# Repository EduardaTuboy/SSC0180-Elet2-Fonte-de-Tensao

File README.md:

# Trabalho 1 - Fonte de tensão variável
Projeto realizado para a disciplina Eletrônica para Computação [SSC0180], ministrado pelo docente [Eduardo Vale Simões](https://gitlab.com/simoesusp), durante o primeiro semestre do curso de Bacharelado em Ciências de Computação, na USP campus São Carlos.

## Integrantes do Grupo 8
* [Eduarda tuboy Nardin](https://github.com/EduardaTNardin) | nº USP 13732495
* [Gabriel Barbosa dos Santos](https://github.com/GotemBarbosa) | nº USP 14613991
* [Guilherme Antonio Costa Bandeira](https://github.com/Guilherme-Bandeira) | nº USP 14575620
* [Rafael Brazolin Alvez Mansur](https://github.com/RafaelMansurUsp)| nº USP 14604020
* [Renan Parpinelli Scarpin](https://github.com/RenanScarpin)| nº USP 14712188

## Objetivo
Montar em uma *protoboard* um circuito que recebe como entrada uma corrente alternada de 127V e retorna como saída uma corrente contínua ajustável entre 3V a 12V, com capacidade de 100mA de corrente.

## Diagrama de fonte no Falstad

Link do circuito no Falstad [aqui](https://tinyurl.com/2mkt75e9).

## Escolha dos Componentes
Todos os componentes, menos o cabo conectado ao transformador, foram comprados na loja “Ca And Ma Componentes Eletrônicos”, localizada em São Carlos.

Quantidade | Componente | Especificações | Preço Unidade
--- | --- | --- | ---
1 | Transformador | Trafo Bivolt 18+18v 500mA | R$ 41,90
1 | Ponte Retificadora | KBP206 2A 600V Tower | R$ 3,80
1 | Capacitor | Elco 680 µF 25V | R$ 5,80
1 | LED | Cristal, cor vermelha | R$ 1,30
1 | Diodo Zenner | 1N47430 [ 13V \ 1W ] | R$ 0,48
1 | Transistor NPN | BD137 [ 60V \ 1,5A ] | R$ 1,40
1 | Potenciômetro 5K | 1W \ B5K | R$ 7,00
2 | Resistor 1K | CR25 Carvão LGE | R$ 0,14
1 | Resistor 2.7K | CR25 Carvão | R$ 0,07
1 | Resistor 6.8K | CR25 Carvão Rohs | R$ 0,07
10 | Jumpers | Femea x Macho | R$ 0,70
1 | Protoboard | BB-01 400P Sem base tower | R$ 20,40
Total | | | R$ 89,36

## Projeto no Software Eagle

## Cálculos e Montagem
De início, é necessário saber a razão Ns / Np, utilizado nas definições do Falstad, sendo Ns número de espiras do enrolamento da bobina secundária e Np número de espiras do enrolamento da bobina primária. Essa razão se dá pela relação:

$\frac{V_p}{N_p}=\frac{V_s}{N_s}$

$\frac{127}{N_p}=\frac{18}{N_s}$

$\frac{N_s}{N_p}=\frac{18}{127} = 7,05$

Depois, é calculada a tensão de pico do circuito, que é a voltagem que sai do transformador vezes raiz de dois subtraindo duas vezes o valor 0,7V, que é a quantidade de tensão dissipada por cada diodo, e já que em cada ciclo a corrente passa por 2 diodos, é necessário multiplicar 0,7V por dois:

$V_{máx} = V_{transformador} \cdot \sqrt{2}-(2 \cdot 0,7 V)$

$V_{máx} = 18 \cdot \sqrt{2}-(1,4)$

$V_{máx} = 24,06 V$

Em seguida, inicia-se a montagem e cálculo do circuito pelo diodo zener, visto que tal componente requer o mínimo de valor de corrente que passa por ele, caso contrário ele pode queimar, e também que passe uma tensão maior que 13V, para que o zener de 13V consiga ligar e fixar a corrente passada por ele em 13V. Assim, com essas condições, foi utilizado o Falstad para ajustar o resistor acima do diodo zener de forma que atinja um valor de resistor comercial e as especificações, sendo este valor 2,7K $\Omega$.

Após isso, foi calculado o resistor logo abaixo do potenciômetro, sendo este necessário para regular o range do potenciômetro entre 3V e 12V, visto que sem tal resistor o range vai de 0V até 13V. Testando no Falstad, chegou-se em 2,2K $\Omega$, porém devido a problemas de mal-contato ocasionados pelos grandes pinos do potenciômetro, foi colocado dois resistores de 1K $\Omega$ em série para gerar 2K $\Omega$ de resistência a fim da fonte entregar 3V quando estiver no mínimo do potenciômetro.

Para calcular o resistor do LED, foi ajustado através do Falstad o valor do resistor que faz com que passe o mínimo de corrente possível e ainda faça com que o LED funcione, sendo esse valor 3mA. Logo, foi concluído que o resistor precisa ser do valor de 6,8K $\Omega$.

Para calcular a capacitância do capacitor, foi utilizado a seguinte fórmula:

$C = Io \cdot (2 \cdot f \cdot V_s \cdot ripple)^{-1}$

* Io - Corrente de saída do capacitor
* Vs - Tensão de pico
* Ripple - Voltagem de ripple
* f - Frequência da fonte

Para a obtenção da corrente, são somadas a corrente no led, no diodo zener e na saída do carregador, todas obtidas pela primeira lei de ohm.

$Io = I_{led} + I_{zener} + I_c$

$I_{led} = \frac{24,06V - 3,1V}{6800\Omega}=0,0031A=3,1mA$

$I_{zener} = \frac{24,06V - 13V}{2700\Omega}=0,0041A =4,1mA$

Pela especificação do problema:

$I_c = 100mA$

Logo, a corrente de saída do capacitor é:

$Io = 3,1mA + 4,1mA + 100mA = 107,2mA$

Voltando á fórmula do capacitor:

$C = Io \cdot (2 \cdot f \cdot V_s \cdot ripple)^{-1}$

$C = 0,1072 \cdot (120 \cdot 24,06 \cdot 0,06)^{-1}$

$C = 0,0006188233F = 618,82\mu F$

Como 618,82 $\mu F$ não é um valor comercial, foi escolhido um capacitor de 680 $\mu F$.

### Esquema do diagrama da fonte

## Vídeo e Fotos da fonte
Vídeo do funcionamento da fonte nesse [link](https://drive.google.com/file/d/1ItndYaJXKqj53ECNaNRtKMORyY3nLMsF/view?usp=sharing)
Fotos no mesmo diretório deste README.

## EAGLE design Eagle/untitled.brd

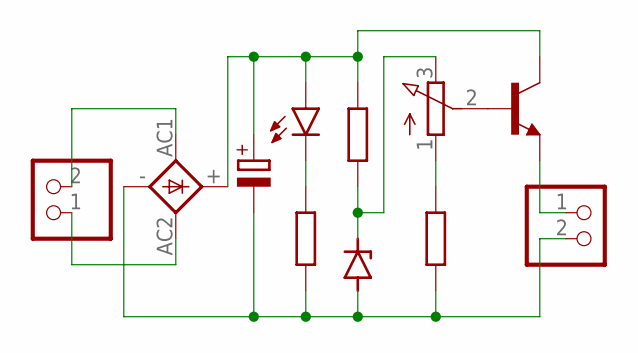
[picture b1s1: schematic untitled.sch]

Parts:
1N47430_13V_1W: 1N4728; DO41Z10
B5K_1W: B5K; 3RP/1610N
BD137_60V_1.5A: BC547; TO92
CR25_2000OHM: 2k; 0207/10
CR25_2700OHM: 2.7k; 0207/10
CR25_6800OHM: 6.8k; 0207/10
ELCO_680UF_25V: 680 uF; E5-10,5
IN: In; 1X02
KBP206_2A_600V_TOWER: 2A 600V; 1KAB
LED_VERMELHO: LedR; LED5MM
OUT: Out; 1X02

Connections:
unnamed: IN.2, KBP206_2A_600V_TOWER.AC1
unnamed: IN.1, KBP206_2A_600V_TOWER.AC2
unnamed: BD137_60V_1.5A.3 (C), CR25_2700OHM.1, ELCO_680UF_25V.+, KBP206_2A_600V_TOWER.+, LED_VERMELHO.A
unnamed: 1N47430_13V_1W.A, CR25_2000OHM.2, CR25_6800OHM.2, ELCO_680UF_25V.-, KBP206_2A_600V_TOWER.-, OUT.2
unnamed: CR25_6800OHM.1, LED_VERMELHO.K (C)
unnamed: 1N47430_13V_1W.C, B5K_1W.3 (E), CR25_2700OHM.2
unnamed: B5K_1W.2 (S), BD137_60V_1.5A.2 (B)
unnamed: B5K_1W.1 (A), CR25_2000OHM.1
unnamed: BD137_60V_1.5A.1 (E), OUT.1

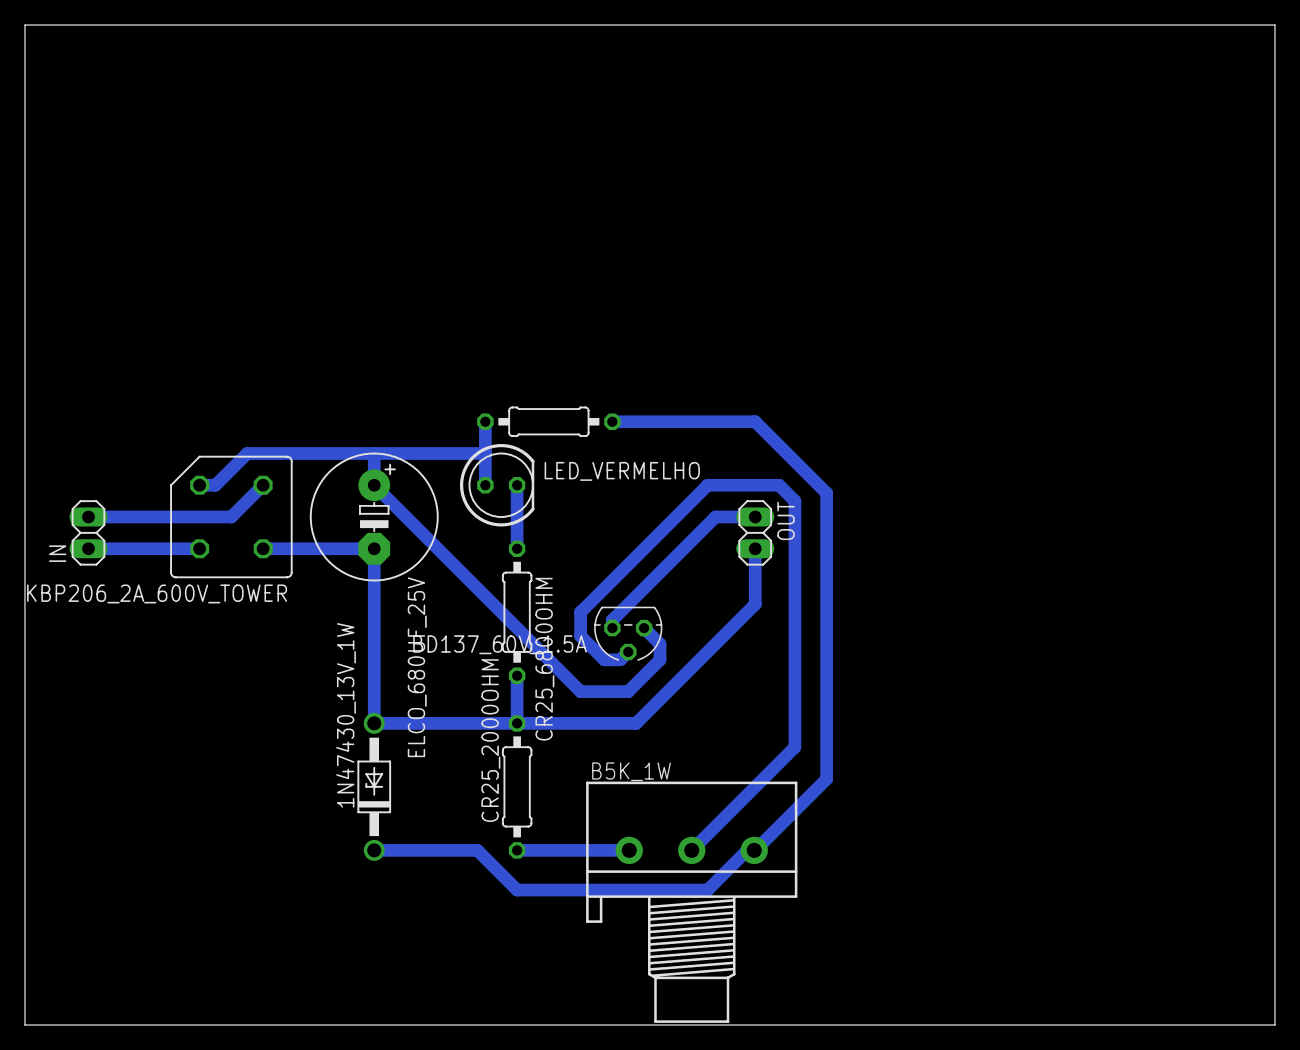
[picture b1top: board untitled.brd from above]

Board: 2 copper layers, 100.0 x 80.0 mm, 11 parts (0 on the bottom side), 9 nets.

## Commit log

2023-04-25 Atualização Inicial Readme
2023-07-02 Create txt
2023-07-02 Added Eagle Files
